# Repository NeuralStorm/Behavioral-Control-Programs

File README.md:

# Behavioral-Control-Programs

# Repo Layout

tilt_hardware_control/tilt_rewrite - tilt task control software  
tilt_hardware_control/tilt_docs - documentation for the tilt task hardware and software  
tilt_hardware_control/si_programmer_scripts - motor controller scripts for tilt task  
Primate_Joystick_Pull - NHP behavior task  
one_targ - center out task

## Related

schematics and board layouts for the voltage conversion board used with tilt_hardware_control are in the [hardware repo](https://github.com/NeuralStorm/hardware/tree/main/conversion_board)

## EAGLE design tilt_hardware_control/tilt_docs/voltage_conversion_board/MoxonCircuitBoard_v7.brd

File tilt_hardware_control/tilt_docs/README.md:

# Hardware Documentation

## Platform Details

The platform consists of three individual plates, covered by a plexiglass layer, which are fixed on top of a number of sensors that rely on [strain gauge](https://en.wikipedia.org/wiki/Strain_gauge) readings to measure the force and torque along the X, Y, and Z axes for each individual sensor. The platforms are arranged in such a way that two limbs on one side (in the context of the Moxon Neurorobotics Laboratory, generally the hindlimbs) may be recorded individually while the two limbs on the other side (generally the forelimbs) are recorded using a single sensor.

## Center of Pressure Calculation

The center of pressure is calculated using a set of equations established in [this paper](https://github.com/NeuralStorm/Behavioral-Control-Programs/blob/kev-readme/tilt_hardware_control/tilt_docs/cop-paper.pdf).

The `x` and `y` coordinates (for each foot placement) are based on the center of each respective sensor, and are offset based on both the location of the sensors relative to each other, and to account for the thickness of the plexiglass layer (using the `z` value).:

Where `F` represents the translation **force** components along their respective axes, and the `T` represents the **torque** component about their respect axes. These individual foot placements and the [Ground Reaction Forces](https://en.wikipedia.org/wiki/Ground_reaction_force)[^grfnote] are then combined to obtain the center of pressure of the entire subject:

## Processing Pipeline

Any data recorded using this set-up is generally fed into [GRF Python](https://github.com/NeuralStorm/Behavior-Analysis-Programs/tree/master/grf_python) (assuming it was recorded the Moxon Neurorobotics tilt task control software), which converts the strain gauge data collected into [Ground Reaction Force](https://en.wikipedia.org/wiki/Ground_reaction_force) data. Related neural data (`.plx`/`.pl2`) is generally fed into the [Matlab Offline Neural Analysis (MONA)](https://github.com/NeuralStorm/MATLAB-offline-neural-analysis) program, which can parse this data and generate relative response matrices, as well as create Peri-Stimulus Time Histograms and run various different kinds of analyses.

[^grfnote]: It is crucial that all users understand that the Ground Reaction Forces are **not** the raw values obtained using the tilt recording software. The Ground Reaction Forces are calculated from the raw strain gauge data the tilt task recording software saves to a `.csv` file.

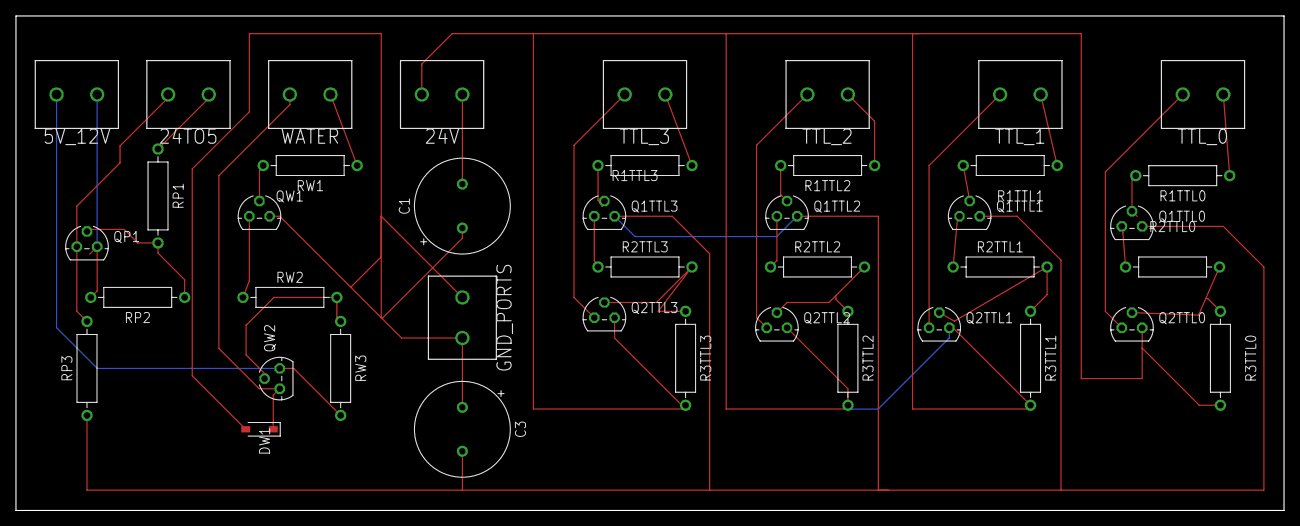
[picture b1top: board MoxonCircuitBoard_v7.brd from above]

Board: 2 copper layers, 158.7 x 61.9 mm, 41 parts (0 on the bottom side), 33 nets.

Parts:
5V_12V: 1_12V_2_5V; TERMBLK_508-2N
24TO5: 1_Mout_2_Min; TERMBLK_508-2N
24V: 1_24V_2_SMPSGround; TERMBLK_508-2N
C1, C3: CAPPRD550W60D1200H2000B
DW1: 1N4148W; SOD3715X135
GND_PORTS: 2828XX-2282837-2; TERMBLK_508-2N
Q1TTL0, Q1TTL1, Q1TTL2, Q1TTL3, Q2TTL0, Q2TTL1, Q2TTL2, Q2TTL3: 2N3904; TO92
QP1: 2N3904; TO92
QW1: 2N3904; TO92
QW2: 2N4401; TO92
R1TTL0, R1TTL1, R1TTL2, R1TTL3: 3.9K_1/4W; RESAD1176W63L850D250B
R2TTL0, R2TTL1, R2TTL2, R2TTL3: 22K_1/4W; RESAD1176W63L850D250B
R3TTL0, R3TTL1, R3TTL2, R3TTL3: 1M_1/4W; RESAD1176W63L850D250B
RP1: 3.9K_1/4W; RESAD1176W63L850D250B
RP2, RP3: 1M_1/4W; RESAD1176W63L850D250B
RW1: 1.2K_1/4W; RESAD1176W63L850D250B
RW2: 470_1/2W; RESAD1176W63L850D250B
RW3: 1M_1/4W; RESAD1176W63L850D250B
TTL_0, TTL_1, TTL_2, TTL_3: 2828XX-2282837-2; TERMBLK_508-2N
WATER: 2828XX-2282837-2; TERMBLK_508-2N

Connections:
GND: C1.1, C3.1, C3.2, DW1.2, GND_PORTS.1, GND_PORTS.2, Q1TTL0.1, Q1TTL1.1, Q1TTL2.1, Q1TTL3.1, QW1.1, RP3.1
unnamed: QP1.2, RP1.2, RP2.1
unnamed: 24V.2, C1.2
unnamed: 24TO5.1, QP1.3, RP3.2
unnamed: 24TO5.2, RP1.1
unnamed: QW1.2, RW1.2
unnamed: QW1.3, RW2.1
unnamed: QW2.2, RW2.2, RW3.1
unnamed: 5V_12V.1, QW2.1, RW3.2
unnamed: DW1.1, QW2.3, WATER.1
unnamed: Q1TTL3.2, R1TTL3.2
unnamed: Q1TTL3.3, R2TTL3.1
unnamed: Q2TTL3.2, R2TTL3.2, R3TTL3.1
unnamed: Q2TTL3.3, TTL_3.1
unnamed: Q1TTL2.2, R1TTL2.2
unnamed: Q1TTL2.3, R2TTL2.1
unnamed: Q2TTL2.2, R2TTL2.2, R3TTL2.1
unnamed: R1TTL3.1, TTL_3.2
unnamed: Q1TTL1.2, R1TTL1.2
unnamed: Q1TTL1.3, R2TTL1.1
unnamed: Q2TTL1.2, R2TTL1.2, R3TTL1.1
unnamed: R1TTL2.1, TTL_2.2
unnamed: Q1TTL0.2, R1TTL0.2
unnamed: Q1TTL0.3, R2TTL0.1
unnamed: Q2TTL0.2, R2TTL0.2, R3TTL0.1
unnamed: 24V.1, Q2TTL0.1, Q2TTL1.1, Q2TTL2.1, Q2TTL3.1, R3TTL0.2, R3TTL1.2, R3TTL2.2, R3TTL3.2
unnamed: Q2TTL2.3, TTL_2.1
unnamed: R1TTL0.1, TTL_0.2
unnamed: Q2TTL0.3, TTL_0.1
unnamed: R1TTL1.1, TTL_1.2
unnamed: Q2TTL1.3, TTL_1.1
unnamed: RW1.1, WATER.2
unnamed: 5V_12V.2, QP1.1, RP2.2

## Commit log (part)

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2020-02-21 Add files via upload
    readyforplexon True
2020-02-27 Add files via upload
    Added Notes for where the PyDaqMx Event Timestamps should be. Will test on 2/27. Need to test task and task2. Commented out task3, not currently in use.
2020-02-27 Add files via upload
    Took out Test2 and Test3 for strobed testing. Have some example code for DS and GC Events, and others to be uncommented for testing.
2020-02-28 Add files via upload
    Most Events going into csv. Small bug where sometimes the end of trial doesnt get added to csv, but it is currently saved in .plx file. Still working to figure out cause, seems random, but mostly it 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
2020-02-28 Add files via upload
    Added reset to Training with DS, STARTSTOP is functional and csv working with slight exceptions on Trial End times( these are correct in plexon .plx files), StartSTOP Events is currently testing wins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
2020-03-02 Add files via upload
    Added Go Cue to Training
2020-03-03 Add files via upload
    Fixed bug in which the Start Trial Blinking + Sound chime was not resetting the sound properly after the first trial. Error was OutofHomeZone == False, instead of = False.
2020-03-03 Add files via upload
    Fixed bug where pausing during first blinking box would cause sound to not come back on when started again.
2020-03-04 Add files via upload
    Runs and saves , but need to compare names of saved variables, add in some placeholders and double check all variables.
2020-03-05 Add files via upload
    Working, checked Timestamps and End of Session CSV vars. Waiting on connector to have t start and t exit into plx as well. Need to check on update speed of the GUI.
2020-03-06 Add files via upload
    Testing why fast in and outs don't trigger t1 failure / how to pop those vals off of the list
2020-03-07 Add files via upload
    DS_GC: Changed format of CSV. Have just about everything except some things that require connector. Small Bug with Go Cue Stimuli.
    Need to bring most of the changes over to joystick program.
2020-03-10 Add files via upload
    Bugs / Fixed Today 3/10/2020:
    Fixed: Runtime Error in Saving CSV: Put whole function in try block.
    Also wrote DictToCSVWriter.py if needed for copying from word doc
    Fixed: Testing Timestamp Shift: 3/10/2020
    Take TS directly form the TTL pulse on Ch 9 and 10 for HandInTime and HandOutTime. *Important* This change requires that the new connector is used for the trial.
    If connector needs to be taken off for any reason refer to Github version on 3/09/2020 for 'working' change with small timstamp shift.
2020-03-10 Add files via upload
    Fixed Trial Filler 'X's to denote t1 and t2 fails.
2020-03-11 Add files via upload
    Updated start stop with reward durations.
    Changed gathering omni data for DS GC.
    With new plexon server settings the programs run faster and are much more responsive.
2020-03-13 Add files via upload
    Added in average and stdev for each ds. added in total trials / correct / incorrect counts for each ds
    Still working on trials lining up with lots of t3 failures. most of the placeholders work, but still seeing odd cases.
2020-03-23 Add files via upload
    Changing CSV, Fixed some of the Trials lining up in csv, took out joystick zone in csv and ds out / gc out.
2020-03-24 Add files via upload
    Added counter for Post t1 fails and post t2 fails per trial, 0 if not a t1 or t2 fail
2020-03-30 Add files via upload
    Somehow didnt have this on here.
2020-03-31 Add files via upload
    Added more error checking, added metadata button. fixed adaptive value changes.
2020-04-02 Add files via upload
    initialize plexon timestamps as floats
2020-04-20 Organized Primate Center Code into new subfolder
    Reorganizing code.
2020-04-21 Added Max Time After Sound
2020-05-06 Change added to for files to be saved to another directory outside of the code directory.
2020-06-08 Started a new file config-file-loading version called MonkeyImages_Joystick_Conf. Resolved issues with file save and correctly assigning booleans from the config file. Version runs and saves. Tested 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
2020-06-17 Added a post-go time-out if clause to set object state to be caught by MaxTimeAfterSound time-out later on in the main loop. This translates to having the trial time-out if the animal waits too long 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
2020-07-22 Incorporates changes to support single stimulus versions of the Joystick and HomezoneExit versions of the task.
2020-07-30 Re-organization of repo directory. Development iterations of code placed in 'development' directory.
2020-08-30 First commit of tilt haradware code 20200803
2020-09-08 update tilt code
2020-09-19 Add dependencies
2020-09-29 add mock and sham modes, add motor control abstraction
2020-10-01 fix motor control
2020-10-02 make template file paths parameters
2020-10-07 online tilt timing fixes, psth fixes
2020-10-19 add images and config options to joystick pull task
2020-11-05 psth add fixed spike wait
2020-11-06 fix fixed spike wait
2020-11-11 tilt: switch to hjson for config file
2021-01-12 joystick: cleanup, manual water
2021-03-20 tilt: replace most args with a config file, improve mock mode, add reward toggle, make grf recording exit cleanly, record input/output file hashes, record arguments/config
2021-04-05 tilt: update readme, propagate errors in grf data recording, misc
2021-04-09 tilt: maybe improve plexon dll loading
2021-04-16 tilt: fix timestamp generation in grf data
2021-04-19 tilt: refactor recording code, add initial live view
2021-04-27 joystick: add homezone exit task, update docs
2021-04-29 joystick: cleanup
2021-05-01 joystick: fixes
2021-05-12 joystick: black background, change image colors, misc
2021-05-14 joystick: remove unused config values, add water on/off UI buttons, update example config and docs, reduce saturation of images, change when sounds are played, re-add Time Out config, add reward dura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
2021-05-19 joystick: don't show prepare image
2021-06-07 joystick: add sound files
2021-06-08 joystick: update requirements
2021-07-10 joystick: add docs from testing/debugging
2021-07-18 add some documentation from box
2021-08-06 joystick: check that log files can be created and doesn't exist, add event log, add partial logs
2021-08-06 joystick: fail immediately if hand removed from home zone before go cue
2021-08-11 joystick: improve reporting of errors in histogram
2021-08-18 joystick: add discrim delay and go cue delay to output csv
2021-08-19 tilt: add --overwrite parameter, misc fixes
2021-08-24 add touchscreen programs
2021-08-25 tilt: add documentation
2021-09-13 joystick: improve layout logic
2021-09-13 joystick: add session info to csv/console output
2021-09-14 joystick: add info window
2021-09-21 tilt: docs, allow command line arguments in config file
2021-09-25 touchscreen: get running on local
2021-09-25 joystick: add trapezoid reward type
2021-09-25 touchscreen: update requirements/readme
2021-09-25 joystick: delete old files
2021-09-25 tilt: add psth test main, adjust sample batch size, update gitignore
2021-09-25 joystick: change test config
2021-09-29 joystick: change csv line endings to \n
2021-10-06 joystick: change info view histogram steps
2021-10-09 joystick: refactor config loading and tk window creation
2021-10-14 touchscreen: change scaling on windows maybe, documentation/formatting, fix juicer duration maybe
2021-10-23 touch: refactor initialization, allow changing displayed peripheral target, move exit target off screen
2021-11-03 tilt: update device number for motor control
2021-12-13 tilt: add delay after starting recording to cover an analysis window
2021-12-17 re-organize tilt code/docs
2021-12-30 Rewrote the readme.
2021-12-30 Removed superfluous words.
2021-12-30 Reworked Summary.
2021-12-30 Formatting fix.
2021-12-30 Created tilt hardware readme.
2022-01-22 joystick: add yellow star (and triangle apparently)
2022-01-29 joystick: add per discrim pull duration metrics
2022-01-31 touchscreen: change to support python 3.8
2022-02-02 touchscreen: add target distance setting
2022-03-01 touchscreen: add config file
2022-03-08 tilt: misc, add tilt sequence config
2022-03-08 touch: add ch_timeout to config
2022-03-17 tilt: add plexon opx client
2022-03-19 touchscreen: fix errors when more than 400 or 500 trials are performed
2022-04-26 update si programmer scripts
2022-04-27 add data collection template
2022-04-27 touch: update comments in example config
2022-05-08 tilt: update plexnet instructions
2022-07-01 joystick: add stimulus image
2022-07-14 tilt: add timeout waiting for tilt from plexon
2022-07-15 tilt: add classification based stimulation
2022-07-15 tilt: update example config
2022-07-26 joystick: adjust image sizing
2022-08-02 tilt: change how classifier templates are handled
2022-08-16 tilt: adjust delays for intan
2022-09-21 update si programmer scrips and data collection template
2022-09-22 tilt: add tilt type digital outputs for plexon, update live graph layout
2022-09-22 tilt: add same second phase stim setting
2022-12-07 tilt: fix intan param upload
2022-12-07 tilt: 3.9 type fix, auto template out path
2022-12-20 tilt: update for gearbox and new sensor ports
2023-01-13 joystick: improve config path selection
2023-01-13 joystick: save plexon timestamp with events from plexon
2023-02-13 joystick: switch to perf_counter from monotonic
2023-02-13 tilt: add motor position tracking (disabled), add random classifier, add classifier config setting
2023-02-28 tilt: move classifiers into package, adjust tilt timing calculation
2023-02-28 touch: add photo marker
2023-04-03 joystick: fix crash
2023-04-04 joystick: optimize template generation
2023-04-05 joystick: adjust photodiode marker behavior
2023-04-07 joystick: adjust photodiode change threshold
2023-04-20 joystick: refactor classification code, improve gen templates command
2023-04-20 joystick: refactor plexon code
2023-04-20 joystick: add per cue classify reward duration
2023-05-09 joystick: fix crash when not classifier disabled
2023-05-16 joystick: split errors for hand removed before discrim/go cue
2023-05-17 joystick: change logic for joystick pulled before cue error
2023-06-11 joystick: add support for data bridge
2023-07-06 joystick: new events saving system
2023-07-06 joystick: restructure as package
2023-07-06 joystick: refactor histogram code, remove old event log code
2023-07-06 joystick: add data bridge reconnect timeout
2023-07-22 joystick: improve external event handling
2023-07-27 joystick: fix plexon imports
2023-07-27 joystick: add disable_plexon_do environment variable
2023-07-27 joystick: fix joystick pull before cue logic
2023-08-03 joystick: record git errors, use external times for debounce, make x button exit game cleanly, remove high level reward buttons, misc cleanup/refactoring
2023-08-15 joystick: misc
2023-08-15 joystick: remove reload config button, wait for joystick to not be pulled to start trial, track homezone exit event
2023-08-17 joystick: move assets into project directory so it is installed with the package
2023-08-18 joystick: change output csv to tsv
2023-08-18 joystick: add marker flash for prep diamond
2023-08-19 joystick: add display_trials tool
2023-08-22 joystick: update pyproject.toml
2023-08-22 joystick: add repo_path environment variable
2023-08-23 joystick: rate limit event file flushes
2023-08-29 joystick: run plexon get data in a separate process
2023-08-30 joystick: update get_event_times tool
2023-09-27 joystick: update photodiode logic
2023-10-10 touch: update install, readme, output path logic
2023-11-13 joystick: improve buffering of spikes
2023-11-15 add timestamp to analog output
2023-12-03 touch: add fake fullscreen, update readme, use butil plexdo, allow nidaq device selection
2023-12-17 touch: add count trials program
2023-12-18 touch: update poetry lock
2023-12-23 fix template generation
2024-01-20 update euclidean classifier logic
2024-01-30 joystick: add baseline-offset setting to template generation, adjust command line options
2024-01-30 improve template generation backward compatibility
2024-01-30 joystick: update version log
2024-02-01 joystick: change default analog recording settings
2024-02-01 joystick: separate event source and digital output
2024-02-01 joystick: documentation update
2024-02-01 tilt: incomplete update of wiring documentation
2024-02-01 move data bridge event source to butil
2024-02-27 update data bridge event source
2024-02-27 allow arbitrary configuration in data bridge
2024-03-28 joystick: re-add bridge channel mapping
2024-04-17 touch: rewrite center out task
2024-05-08 touch: add center target reward, improve fullscreen on ubuntu, update hotkeys, add bridge reward output, add touch screen input handling, change how target position is recorded, add peripheral target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
2024-05-28 update version log
2024-06-28 joystick: add test images
